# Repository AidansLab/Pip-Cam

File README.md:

# $\Huge{\textbf{Pip-Cam}}$
Your companion for documenting the wasteland ~~and your untimely demise~~

The Pip-Cam is a small camera module that plugs into the USB-C port of a Pip-Boy (MK V or Pip-Boy 3000). It takes a grayscale photo, dithers it down to the Pip-Boy's screen format, and uploads it straight to the Pip-Boy's filesystem. You can then browse and delete photos from a Pip-Cam app on the Pip-Boy, and re-tune the brightness and contrast of the latest photo.

| Pip-Cam MK V | Pip-Cam 3000 |
| --- | --- |
| See page 1 of [Pip-Cam_Manuals.pdf](Pip-Cam_Manuals.pdf) | See page 2 of [Pip-Cam_Manuals.pdf](Pip-Cam_Manuals.pdf) |

---

## Contents

- [How it works](#how-it-works)
- [Repository layout](#repository-layout)
- [Bill of materials](#bill-of-materials)
- [Ordering the PCBs](#ordering-the-pcbs)
- [Assembly](#assembly)
- [Programming the firmware](#programming-the-firmware)
- [Installing the Pip-Boy app](#installing-the-pip-boy-app)
- [Using the Pip-Cam](#using-the-pip-cam)
- [Troubleshooting](#troubleshooting)
- [License](#license)

---

## How it works

```
 ┌──────────────┐  BAT   ┌──────────────────────────┐  D+/D-  ┌──────────────┐
 │ 3.7V LiPo    ├───────►│ XIAO ESP32-S3 Sense      ├────────►│ USB-C plug   │
 │ 500 mAh      │        │  • OV3660 camera         │         │ breakout     ├──► Pip-Boy
 │ (JST-SH 2p)  │        │  • USB host (native USB) │  VBUS   │ (Adafruit    │
 └──────┬───────┘        │                          │ ┌──────►│  5978)       │
        │                │  D3 ◄── Button ── 3V3    │ │       └──────────────┘
        │                │  D4 ──EN──┐              │ │
        │                └───────────┼──────────────┘ │
        │                      ┌─────▼──────┐         │
        └─────────────────────►│ 5V boost   ├─────────┘
                       VIN     │ (U1V11F5)  │ VOUT
                               └────────────┘
```

- **XIAO ESP32-S3 Sense:** runs the firmware, drives the camera, and acts as a **USB host**. The Pip-Boy shows up to it as a USB serial device (an Espruino console).
- **5 V boost regulator (Pololu U1V11F5):** turns the LiPo voltage into 5 V on the USB-C plug's VBUS, which powers the Pip-Boy's USB port. The XIAO switches it on and off with `D4` (`EN`). A 100 kΩ pull-down (R1, the R6 resistor taken off the regulator) keeps it off while the XIAO is asleep.
- **Shutter button:** connects `3V3` to `D3` (GPIO4). A press both takes a photo and wakes the XIAO from deep sleep.
- **Battery:** a 3.7 V 500 mAh TinyCircuits LiPo on the JST-SH connector (J3), wired to the XIAO's `BAT` pad. Plugging the XIAO's own USB-C into a charger charges it.

Each photo is captured at 480×320 grayscale, center-cropped to **400×208**, adjusted for brightness and contrast, and Floyd–Steinberg dithered to **2 bits per pixel**. It is then sent to the Pip-Boy as `IMGS/<timestamp>.img` using Espruino's packet file-transfer protocol.

## Repository layout

| Path | What it is |
| --- | --- |
| [Pip-Cam_Firmware/](Pip-Cam_Firmware/) | Arduino sketch for the XIAO ESP32-S3 Sense |
| [Pip-Cam_Firmware/Pip-Cam_Firmware.ino](Pip-Cam_Firmware/Pip-Cam_Firmware.ino) | Main state machine: USB host, capture, upload, sleep |
| [Pip-Cam_Firmware/ImageConverter.h](Pip-Cam_Firmware/ImageConverter.h) | Crop, brightness/contrast, and dithering to the `.img` format |
| [Pip-Cam_Firmware/camera_pins.h](Pip-Cam_Firmware/camera_pins.h) | Camera pin maps (`CAMERA_MODEL_XIAO_ESP32S3` is the one used) |
| [Pip-Cam_Board/](Pip-Cam_Board/) | KiCad projects |
| `Pip-Cam_MainBoard.*` | Main board (XIAO, connectors, R1) |
| `Pip-Cam_Button.*` | Small shutter-button board |
| `Pip-Cam_Panelized_Edge-to-board.*` | **Production panel:** main board and button board on one panel |
| [Pip-Cam_Board/production/](Pip-Cam_Board/production/) | Gerber zip, BOM, and pick-and-place files for fab and assembly |
| [Pip-Cam_Board/Fab/](Pip-Cam_Board/Fab/) | Loose Gerber and drill files for the panel |
| `*.step` / `*.stp` | 3D models of the boards and the off-board parts |
| [Pip-Cam_3D_Files/](Pip-Cam_3D_Files/) | STL files for the shell, the button plunger and the Pip-Boy adapters |
| [Pololu-R6.jpg](Pololu-R6.jpg) | Shows which resistor to take off the Pololu regulator to use as R1 |
| [Pip-Cam_Manuals.pdf](Pip-Cam_Manuals.pdf) | End-user manuals for the MK V and 3000 versions |
| [LICENSE](LICENSE), [LICENSES/](LICENSES/) | Which license covers what, and the full license texts |

## Bill of materials

| Qty | Part | Link |
| --- | --- | --- |
| 1 | Pip-Cam PCB (see [Ordering the PCBs](#ordering-the-pcbs)) | — |
| 1 | Seeed Studio **XIAO ESP32-S3 Sense** | [seeedstudio.com](https://www.seeedstudio.com/XIAO-ESP32S3-Sense-p-5639.html) |
| 1 | **Pololu U1V11F5**: 5 V step-up voltage regulator | [pololu.com/product/2562](https://www.pololu.com/product/2562) |
| 1 (2 for the 3000 adapter) | **Adafruit 5978**: USB Type-C plug breakout | [adafruit.com/product/5978](https://www.adafruit.com/product/5978) |
| 1 (3000 adapter only) | Female USB-C socket | [amazon.com/dp/B0B4J5NJ2Y](https://www.amazon.com/dp/B0B4J5NJ2Y) |
| 1 | TinyCircuits **lithium-ion polymer battery, 3.7 V 500 mAh** | [tinycircuits.com](https://tinycircuits.com/products/lithium-ion-polymer-battery-3-7v-500mah?variant=8736484327515) |
| 1 | JST **SM02B-SRSS-TB**: 2-pin 1.0 mm SH right-angle connector (battery) | [digikey.com](https://www.digikey.com/en/products/detail/jst-sales-america-inc/SM02B-SRSS-TB/926708) |
| 1 | Alps **SKQG** tact switch with stem (any SKQG works, e.g. SKQGABE010) | [digikey.com](https://www.digikey.com/en/products/detail/alps-alpine/SKQGABE010/19529161) |
| 1 | 1/16 in acrylic rod, cut to 5 mm (LED light pipe) | — |
| 1 | M3-0.5 × 8 mm screw (3000 adapter only) | — |
| 1 | M1-0.25 × 3 mm screw (closes the shell) | [mcmaster.com/91430A150](https://www.mcmaster.com/91430A150/) |
| 1 | M1-0.25 nut | [mcmaster.com/90591A311](https://www.mcmaster.com/90591A311/) |
| — | 3D-printed parts (see [3D-printed parts](#3d-printed-parts)) | [Pip-Cam_3D_Files/](Pip-Cam_3D_Files/) |

R1 (100 kΩ) is not a separate purchase: it is taken off the Pololu regulator (see [Assembly](#assembly)).

### 3D-printed parts

| File | Needed for | Purpose |
| --- | --- | --- |
| [Shell_Left.stl](Pip-Cam_3D_Files/Shell_Left.stl) | All | Left shell half. Holds the light pipe. |
| [Shell_Right.stl](Pip-Cam_3D_Files/Shell_Right.stl) | All | Right shell half. Has the slot for the M1 nut on the inside. |
| [Button_Plunger.stl](Pip-Cam_3D_Files/Button_Plunger.stl) | All | Shutter button plunger that presses S1 |
| [MKV_Adaptor.stl](Pip-Cam_3D_Files/MKV_Adaptor.stl) | MK V | Adapter for the Pip-Boy MK V |
| [3000_AdapterTop.stl](Pip-Cam_3D_Files/3000_AdapterTop.stl) | 3000 | Top half of the Pip-Boy 3000 adapter |
| [3000_AdapterBottom.stl](Pip-Cam_3D_Files/3000_AdapterBottom.stl) | 3000 | Bottom half of the Pip-Boy 3000 adapter |
| [3000_AdapterBottom_Spacer_Version.stl](Pip-Cam_3D_Files/3000_AdapterBottom_Spacer_Version.stl) | 3000 | Use instead of `3000_AdapterBottom` if your Pip-Boy has the cuff spacer fitted |

### Where each part goes on the PCB

| Ref | Part | Footprint / connection | Notes |
| --- | --- | --- | --- |
| U1 | XIAO ESP32-S3 Sense | XIAO-ESP32S3-SMD | Must be the *Sense* (camera + PSRAM). Soldered flat as an SMD module, using its underside USB D+/D- and BAT pads. |
| R1 | 100 kΩ resistor (R6 from the Pololu U1V11F5) | 0603 | Pull-down on the boost `EN` line |
| S1 | Alps SKQG tact switch with stem | SW_SPST_SKQG_WithStem | Shutter button, on the button board |
| J1 | Pololu U1V11F5 | 1×4, 2.54 mm | 1 `EN` · 2 `VIN` (BAT) · 3 `GND` · 4 `VOUT` |
| J2 | Adafruit 5978 | 1×5, 2.54 mm | 1 `VBUS` (VOUT) · 2 n/c · 3 `D+` · 4 `D-` · 5 `GND` |
| J3 | SM02B-SRSS-TB | SM02BSRSSTBLFSN | Battery connector. Pin 1 = GND, pin 2 = BAT. |

## Ordering the PCBs

The board is a 2-layer, 1.6 mm FR-4 design. The panel `Pip-Cam_Panelized_Edge-to-board` has the main board and the button board together. The production files were generated with the KiCad *Fabrication Toolkit* plugin in a JLCPCB-ready format.

1. Upload [Pip-Cam_Board/production/Pip-Cam_Panelized_Edge-to-board.zip](Pip-Cam_Board/production/Pip-Cam_Panelized_Edge-to-board.zip) as the Gerber file. Order a **stencil** with it: R1 and the XIAO are reflowed with solder paste.
2. *(Optional, for PCB assembly)* Upload [bom.csv](Pip-Cam_Board/production/bom.csv) and [positions.csv](Pip-Cam_Board/production/positions.csv). The BOM has no LCSC part numbers, so you will have to match the parts by hand. Normally all three parts are hand-placed, and R1 comes off the Pololu regulator, so assembly from the fab is not needed.
3. To regenerate the outputs after changing the design, open `Pip-Cam_Panelized_Edge-to-board.kicad_pro` in KiCad 8+ and run Fabrication Toolkit. Its settings are in [fabrication-toolkit-options.json](Pip-Cam_Board/fabrication-toolkit-options.json).

## Assembly

1. **Separate the panel** into the main board and the button board, and clean up the break-off tabs.
2. **Take R6 off the Pololu U1V11F5.** Put the regulator on a hot plate and remove the 100 kΩ resistor marked **R6** in [Pololu-R6.jpg](Pololu-R6.jpg) (printed `01D`). Keep it: it becomes R1.
3. **Reflow R1 and the XIAO together on a hot plate.**
   > ⚠️ **Remove the camera module (the Sense expansion board) from the XIAO before soldering.** Heating the XIAO with the camera fitted is dangerous. Attach the camera only after all soldering is done (step 8).

   Apply solder paste to the main board with the stencil. Place R1 (the resistor from step 2) and the bare XIAO ESP32-S3 on their footprints, then reflow both on the hot plate in one pass. The XIAO's **underside pads** must reflow as well as its castellated edges, because the USB `D+`/`D-` and `BAT` pads carry signals on this board.

   S1 (the SKQG switch) on the button board can be reflowed on the hot plate too, or soldered with an iron later in step 7.
4. **J3 (battery connector).** Solder J3 on the main board **with an iron**. It can't go on the hot plate.
5. **5 V boost regulator (J1).** Mount the Pololu U1V11F5 (with R6 already removed) using the header pins that come with it, matching `EN`, `VIN`, `GND` and `VOUT` to the silkscreen:
   1. Push the header through the main board so the black plastic spacer is on the side **opposite** the regulator (same side as the XIAO). The spacer holds the pins straight.
   2. Put the regulator on the pins on the other side, flush against the main board, and solder the **regulator** side.
   3. Pull the black spacer off the pins.
   4. Solder the **main board** side and trim the excess pins.
6. **USB-C plug (J2).** Mount the Adafruit 5978 breakout using the header that comes with it. This works the opposite way to the regulator, with the breakout soldered last:
   1. Put the header, with its black spacer, through the breakout. Push the pins through the main board.
   2. Solder the pins on the **main board** side, opposite the breakout.
   3. Pull the black spacer off, press the breakout flush, and solder the **breakout** side.
7. **Button board (do this last, before plugging in the battery).**
   - If S1 wasn't reflowed in step 3, solder it now with an iron.
   - The fingers on the button board slot into the main board. They often need **filing** before they fit.
   - Fit the button board so the switch faces **up**, the same direction as the XIAO's USB-C port.
   - Solder its two pads to the main board.
8. **Attach the camera.** Once all soldering is finished and the board has cooled, fit the camera module (Sense expansion board) back onto the XIAO.
9. **Battery and test.** Plug the TinyCircuits 500 mAh LiPo into J3. J3 expects pin 1 = **GND** and pin 2 = **BAT+**. Check the polarity with a meter first, especially if you use a different battery: JST-SH batteries are sold wired both ways. Then check, before closing the case:
   - The XIAO's orange LED should blink at about 1 Hz for 10 s while it looks for the Pip-Boy, then stop blinking (deep sleep). Pressing the shutter button should wake it again.
   - While it is awake, VBUS on the USB-C plug should read about 5 V. While it is asleep, it should read about 0 V.
10. **Light pipe.** Ream the light-pipe hole in `Shell_Left` to size with a small drill bit. Glue in the 5 mm piece of 1/16 in acrylic rod.
11. **Close the shell.** Fit the button plunger and the electronics into the shell halves. Put the M1 nut in the slot on the inside of `Shell_Right`, then screw the halves together at the bottom with the M1 × 3 mm screw.
12. **Adapter.**
    - **MK V:** use `MKV_Adaptor`.
    - **3000:** wire the female USB-C socket to the second Adafruit USB-C plug breakout, then place both in the adapter. Assemble `3000_AdapterTop` and `3000_AdapterBottom` (or the spacer version) with the M3 × 8 mm screw.

    Then attach the Pip-Cam as shown in [Pip-Cam_Manuals.pdf](Pip-Cam_Manuals.pdf).

## Programming the firmware

### 1. Install the toolchain

1. Install the **Arduino IDE 2.x**.
2. In *Boards Manager*, install **esp32 by Espressif Systems**, version **3.x**. The USB host library depends on ESP-IDF 5.
3. Install the **USBHostSerial** library by Bert Melis ([github.com/bertmelis/USBHostSerial](https://github.com/bertmelis/USBHostSerial)), either from the Library Manager or as a ZIP via *Sketch → Include Library → Add .ZIP Library*.
   `esp_camera` and `mbedtls` come with the ESP32 core.

### 2. Board settings (*Tools* menu)

| Setting | Value |
| --- | --- |
| Board | **XIAO_ESP32S3** |
| PSRAM | **OPI PSRAM** (required: the frame buffer lives in PSRAM) |
| Flash Size | 8MB |
| Partition Scheme | Default |
| USB CDC On Boot | Enabled |

### 3. Upload

1. Open [Pip-Cam_Firmware/Pip-Cam_Firmware.ino](Pip-Cam_Firmware/Pip-Cam_Firmware.ino).
2. Unplug the battery, then connect the XIAO's **own** USB-C port to your computer.
3. Put the XIAO into the bootloader: **hold BOOT, plug in the USB, then release BOOT.**
   This step is needed because the firmware takes over the ESP32-S3's native USB for host mode and also deep-sleeps most of the time. The port it would normally show up on doesn't exist while the firmware is running.
4. Select the port and click **Upload**.
5. Unplug the XIAO and plug in the battery, the orange light should start to blink.

The firmware has no serial logging, because the USB port is busy talking to the Pip-Boy. Use the orange user LED to see what it is doing:

| LED | Meaning |
| --- | --- |
| Blinking ~1 Hz | Awake, waiting for the Pip-Boy over USB (gives up after 10 s) |
| Steady or off (not blinking) | Connected and idle, or in deep sleep |
| Fast flicker | Uploading a photo to the Pip-Boy |

### Tunables

These are at the top of `Pip-Cam_Firmware.ino`:

| Constant | Default | Purpose |
| --- | --- | --- |
| `CONVERT_BPP` | `2` | Output bit depth (1, 2, 4 or 8). The Pip-Boy app expects 2. |
| `CONVERT_BRIGHTNESS` / `CONVERT_CONTRAST` | `0` | Defaults used when the Pip-Boy sends no values |
| `SLEEP_TIMEOUT` | `60000` ms | Idle time while connected before deep sleep |
| USB connect timeout (in `STATE_WAIT_USB`) | `10000` ms | How long to look for the Pip-Boy after waking |
| `ACK_TIMEOUT` | `2000` ms | Upload is abandoned if the Pip-Boy doesn't ACK a packet in time |

The firmware writes OV3660 registers directly (`0x3008` software power-down). The camera is also flipped vertically (`set_vflip`) to suit how it is mounted in the shell. If your XIAO Sense came with the older OV2640 sensor, those register writes do nothing. Capture still works, but standby current will be higher.

## Installing the Pip-Boy app

The Pip-Boy needs the Pip-Cam app, which handles the button events and the photo viewer. Install it with the **Pip-Cam Module Installer**: scan the QR code in [Pip-Cam_Manuals.pdf](Pip-Cam_Manuals.pdf) and open the link **on a computer**. The installer connects to the Pip-Boy over USB from the browser.

The Pip-Boy app source is in a separate repository, [AidansLab/Pip-Boy-CFW-Builder](https://github.com/AidansLab/Pip-Boy-CFW-Builder):

| Pip-Boy | App source |
| --- | --- |
| Pip-Boy 3000 | [`/camera`](https://github.com/AidansLab/Pip-Boy-CFW-Builder/tree/main/camera) |
| Pip-Boy MK V | [`/Patches`](https://github.com/AidansLab/Pip-Boy-CFW-Builder/tree/main/Patches) |

## Using the Pip-Cam

1. Plug the Pip-Cam into the Pip-Boy.
   - **Pip-Boy 3000:** plug in through the adapter. When removing it, **pull out the adapter with the Pip-Cam still attached, then detach the Pip-Cam**.
2. Press the shutter button to wake the camera. The XIAO powers the Pip-Boy's USB port, finds the Pip-Boy, and the Pip-Cam footer appears.
3. Open the Pip-Cam app and take photos with the shutter button.

| Control | MK V | 3000 |
| --- | --- | --- |
| Capture photo | Shutter button on the Pip-Cam | Shutter button on the Pip-Cam |
| Brightness | Scroll left wheel | Capture mode: scroll left wheel |
| Reconvert last photo with new settings | Click left wheel | Capture mode: click left wheel |
| Contrast | Right-side knob | Capture mode: right-side knob |
| Next / previous image | Right wheel up/down | Photos mode: right-side knob |
| Delete menu | Click right wheel | Photos mode: click left wheel (scroll to choose) |
| Switch mode | — | Hold left wheel |
| Exit app | Power button | Power button |

> **Note:** Reconvert only works on the **latest** photo, not on older ones in the gallery. The Pip-Cam keeps only the most recent raw capture, in RAM, and re-dithers it with the new brightness and contrast. That capture is lost when the Pip-Cam goes to sleep, so re-tune a photo before the camera times out.

The camera goes back to deep sleep after 60 s with no activity. Press the shutter button to wake it.

## Troubleshooting

| Symptom | Likely cause |
| --- | --- |
| Arduino can't find a port or upload fails | Enter the bootloader: hold BOOT while plugging in the USB |
| LED blinks for 10 s, then stops, and the Pip-Boy shows nothing | No USB link. Check the J2 header joints on both the main board and the breakout (D+ and D-), that VBUS reaches about 5 V while awake, and the J1 regulator joints (especially `EN`). |
| Nothing at all when pressing the button | Battery flat or connected backwards (check J3 polarity), or the button board isn't connected to D3/3V3 |
| Photo upside down | Remove or flip `s->set_vflip(s, 1)` in `setup()` to suit your mounting |
| Camera init fails or no photo | PSRAM not set to **OPI PSRAM**, or the camera module isn't fully seated on the XIAO |
| Upload stops partway | The Pip-Boy didn't ACK within 2 s. Check the SD card has free space and that the Pip-Cam app is installed. |

## License

| Part | License |
| --- | --- |
| Firmware ([Pip-Cam_Firmware/](Pip-Cam_Firmware/)) | [GPL-3.0-or-later](LICENSES/GPL-3.0.txt) |
| Hardware ([Pip-Cam_Board/](Pip-Cam_Board/), [Pip-Cam_3D_Files/](Pip-Cam_3D_Files/)) and documentation | [CERN-OHL-S-2.0](LICENSES/CERN-OHL-S-2.0.txt) |

Third-party 3D models and images are excluded. See [LICENSE](LICENSE) for details.

Support: contact@aidan.calamera.com

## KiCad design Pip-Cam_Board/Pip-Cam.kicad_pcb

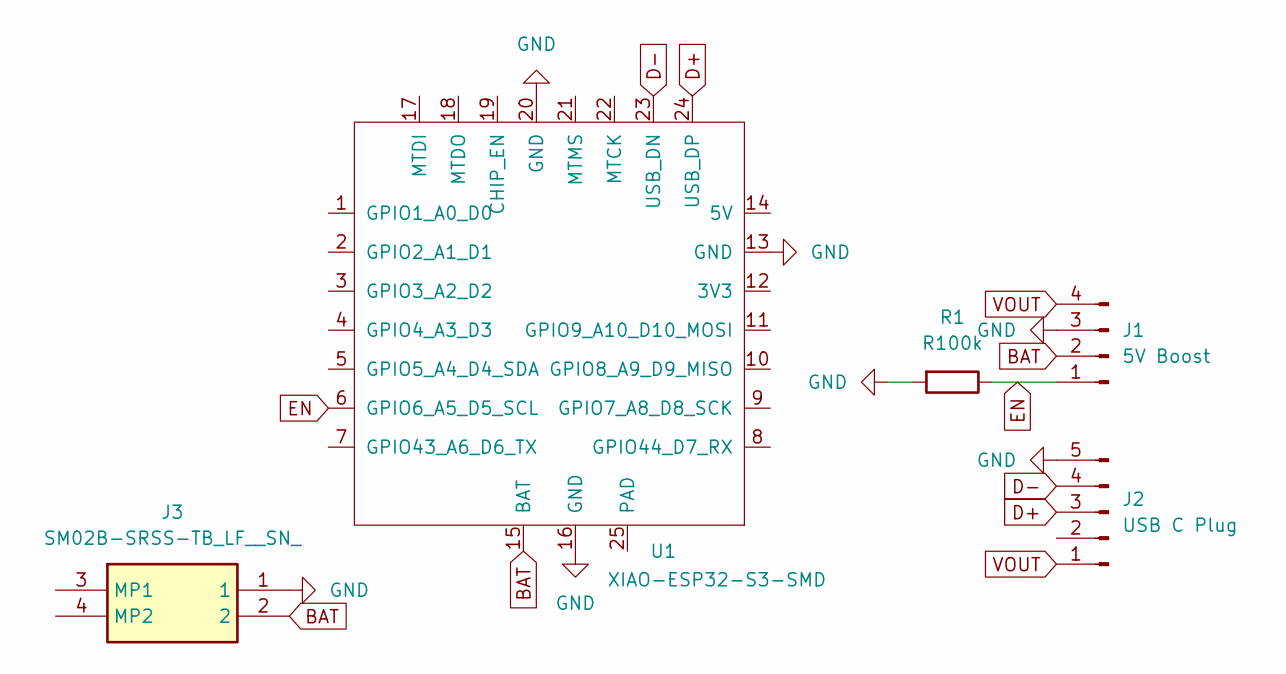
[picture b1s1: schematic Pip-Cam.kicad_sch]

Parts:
J1: 5V Boost; PinHeader_1x04_P2.54mm_Vertical
J2: USB C Plug; PinHeader_1x05_P2.54mm_Vertical
J3: SM02B-SRSS-TB_LF__SN_; SM02BSRSSTBLFSN; Mouser Part Number N/A
R1: R100k; R_0603_1608Metric
U1: XIAO-ESP32-S3-SMD; XIAO-ESP32S3-SMD

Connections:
BAT: J1.2, J3.2, U1.15 (BAT)
D+: J2.3, U1.24 (USB_DP)
D-: J2.4, U1.23 (USB_DN)
EN: J1.1, R1.1, U1.5 (GPIO5_A4_D4_SDA), U1.6 (GPIO6_A5_D5_SCL)
GND: J1.3, J2.5, J3.1, R1.2, U1.13 (GND), U1.16 (GND), U1.20 (GND)
VOUT: J1.4, J2.1

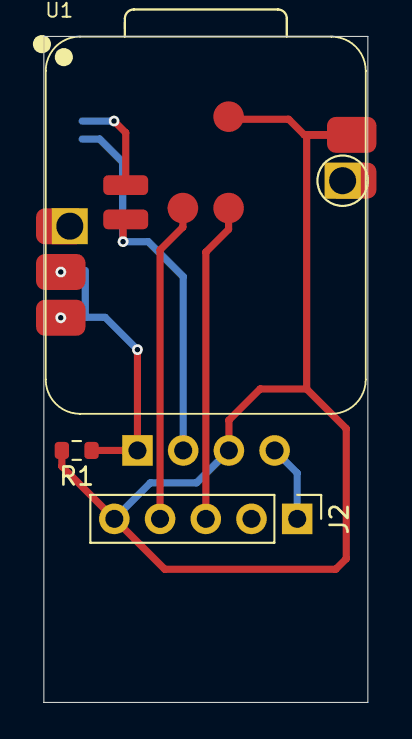
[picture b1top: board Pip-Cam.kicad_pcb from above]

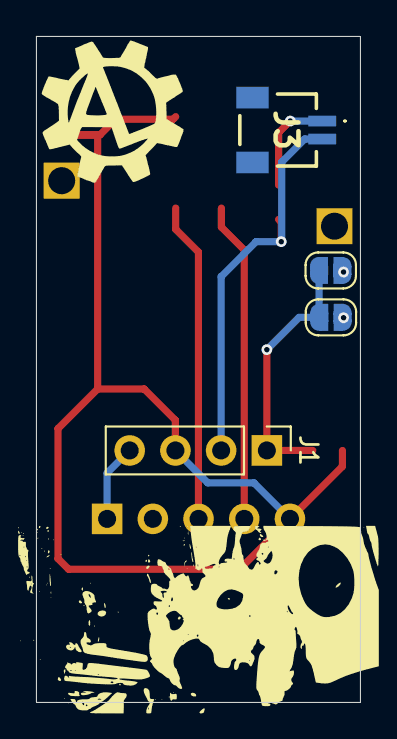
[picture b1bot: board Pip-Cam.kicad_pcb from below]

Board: 2 copper layers, 18.0 x 37.0 mm, 5 parts (2 on the bottom side), 6 nets.

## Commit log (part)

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2025-12-15 Possibly extremely broken.
2026-01-16 Initial push, Pip-Cam firmware V0.4.
2026-01-16 Added Pip-Cam board files.
2026-02-16 Fixed handshake possibly, fingers crossed.
2026-04-02 Firmware V0.9
